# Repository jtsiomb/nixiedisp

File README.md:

nixiedisp - USB nixie tube display
==================================

Nixiedisp is a 6-digit nixie tube numeric display, software-controlled over USB
or RS232, that also functions standalone as a clock.

Features:
  - Controlled over USB or RS232 serial port to display arbitrary numbers, set
    the time/date, change settings, and switch between modes of operation.
  - Standalone operation as a clock or stopwatch timer with a battery-backed
    real-time clock (CR2032 coin cell).
  - Designed to use soviet IN-14 nixie tubes.
  - Powered by a 12v DC supply through a standard 2mm barrel jack (center-positive).

Excercise caution when operating without an enclosure, there are high voltages
(180V DC) present in the power supply section of the board, and around the
nixie tubes.

Project website: http://nuclear.mutantstargoat.com/hw/nixiedisp  
Github repo: https://github.com/jtsiomb/nixiedisp  

Project structure:

 - `hw/`: hardware design
 - `fw/`: firmware for the on-board AVR microcontroller
 - `sw/`: end-user host-side software for controlling the device from a computer

License
-------
Copyright (C) 2020-2021 John Tsiombikas <nuclear@member.fsf.org>

Hardware designs and software (firmware) in this project are free. Feel free to
use, modify, and/or redistribute under the terms of the GNU General Public
License v3, or at your option any later version published by the Free Software
Foundation. See COPYING for details.

How to build a nixiedisp device
-------------------------------
To build one of these for yourself, you need to:

  1. Zip up the contents of the `hw/gerber` directory, and send them to a PCB
     manufacturer to get boards made. For my own boards I used `jlcpcb.com`.

  2. Order the components listed in the bill of materials (`hw/bom.ods`). I
     ordered mine from `mouser.com`, and the spreadsheet contains the mouser
     reference number for each component, to make it easy to order the whole lot
     without too much searching. Make sure to order at least as many of each one
     of them, as specified in the bom.

  3. Find 6 (optionally 4) soviet IN-14 nixie tubes. They tend to go for about
     $10 - $15 each on ebay.

  4. Find a 12v DC power supply with a barrel jack (2mm center pin),
     center-positive (`+ -o)- -`), to power the board. It doesn't have to be
     regulated, but it must be able to provide about 500mA at 12v.
     Typical power consumption is 2-3W.

  5. If you got the git version of this project, you'll need to build the
     firmware by changing into `fw` and typing `make`. You'll need to have
     `avr-gcc`, `libc-avr`, and GNU make installed for this. Release archives
     include a pre-built firmware image you can use (`fw/nixiedisp.hex`).

  6. Assemble the board, and program the microcontroller with a suitable AVR
     ISP. If you have `avrdude` installed, you can simply change into `fw` and
     type `make program`, with the board powered up and the programmer
     connected.

If you don't need the serial port (RS232) option, you can leave J1 (the DB9
connector), U2 (max232 level converter) and all its surrounding electrolytic
capacitors (C1, C2, C4, C8 and C15) unpopulated, and install a 10k pull-up
resistor across the pads of J7 (usbpwr).

References
----------
High-voltage power supply based on Michael Moorrees' nixie supply MK1.5:
https://threeneurons.wordpress.com/nixie-power-supply

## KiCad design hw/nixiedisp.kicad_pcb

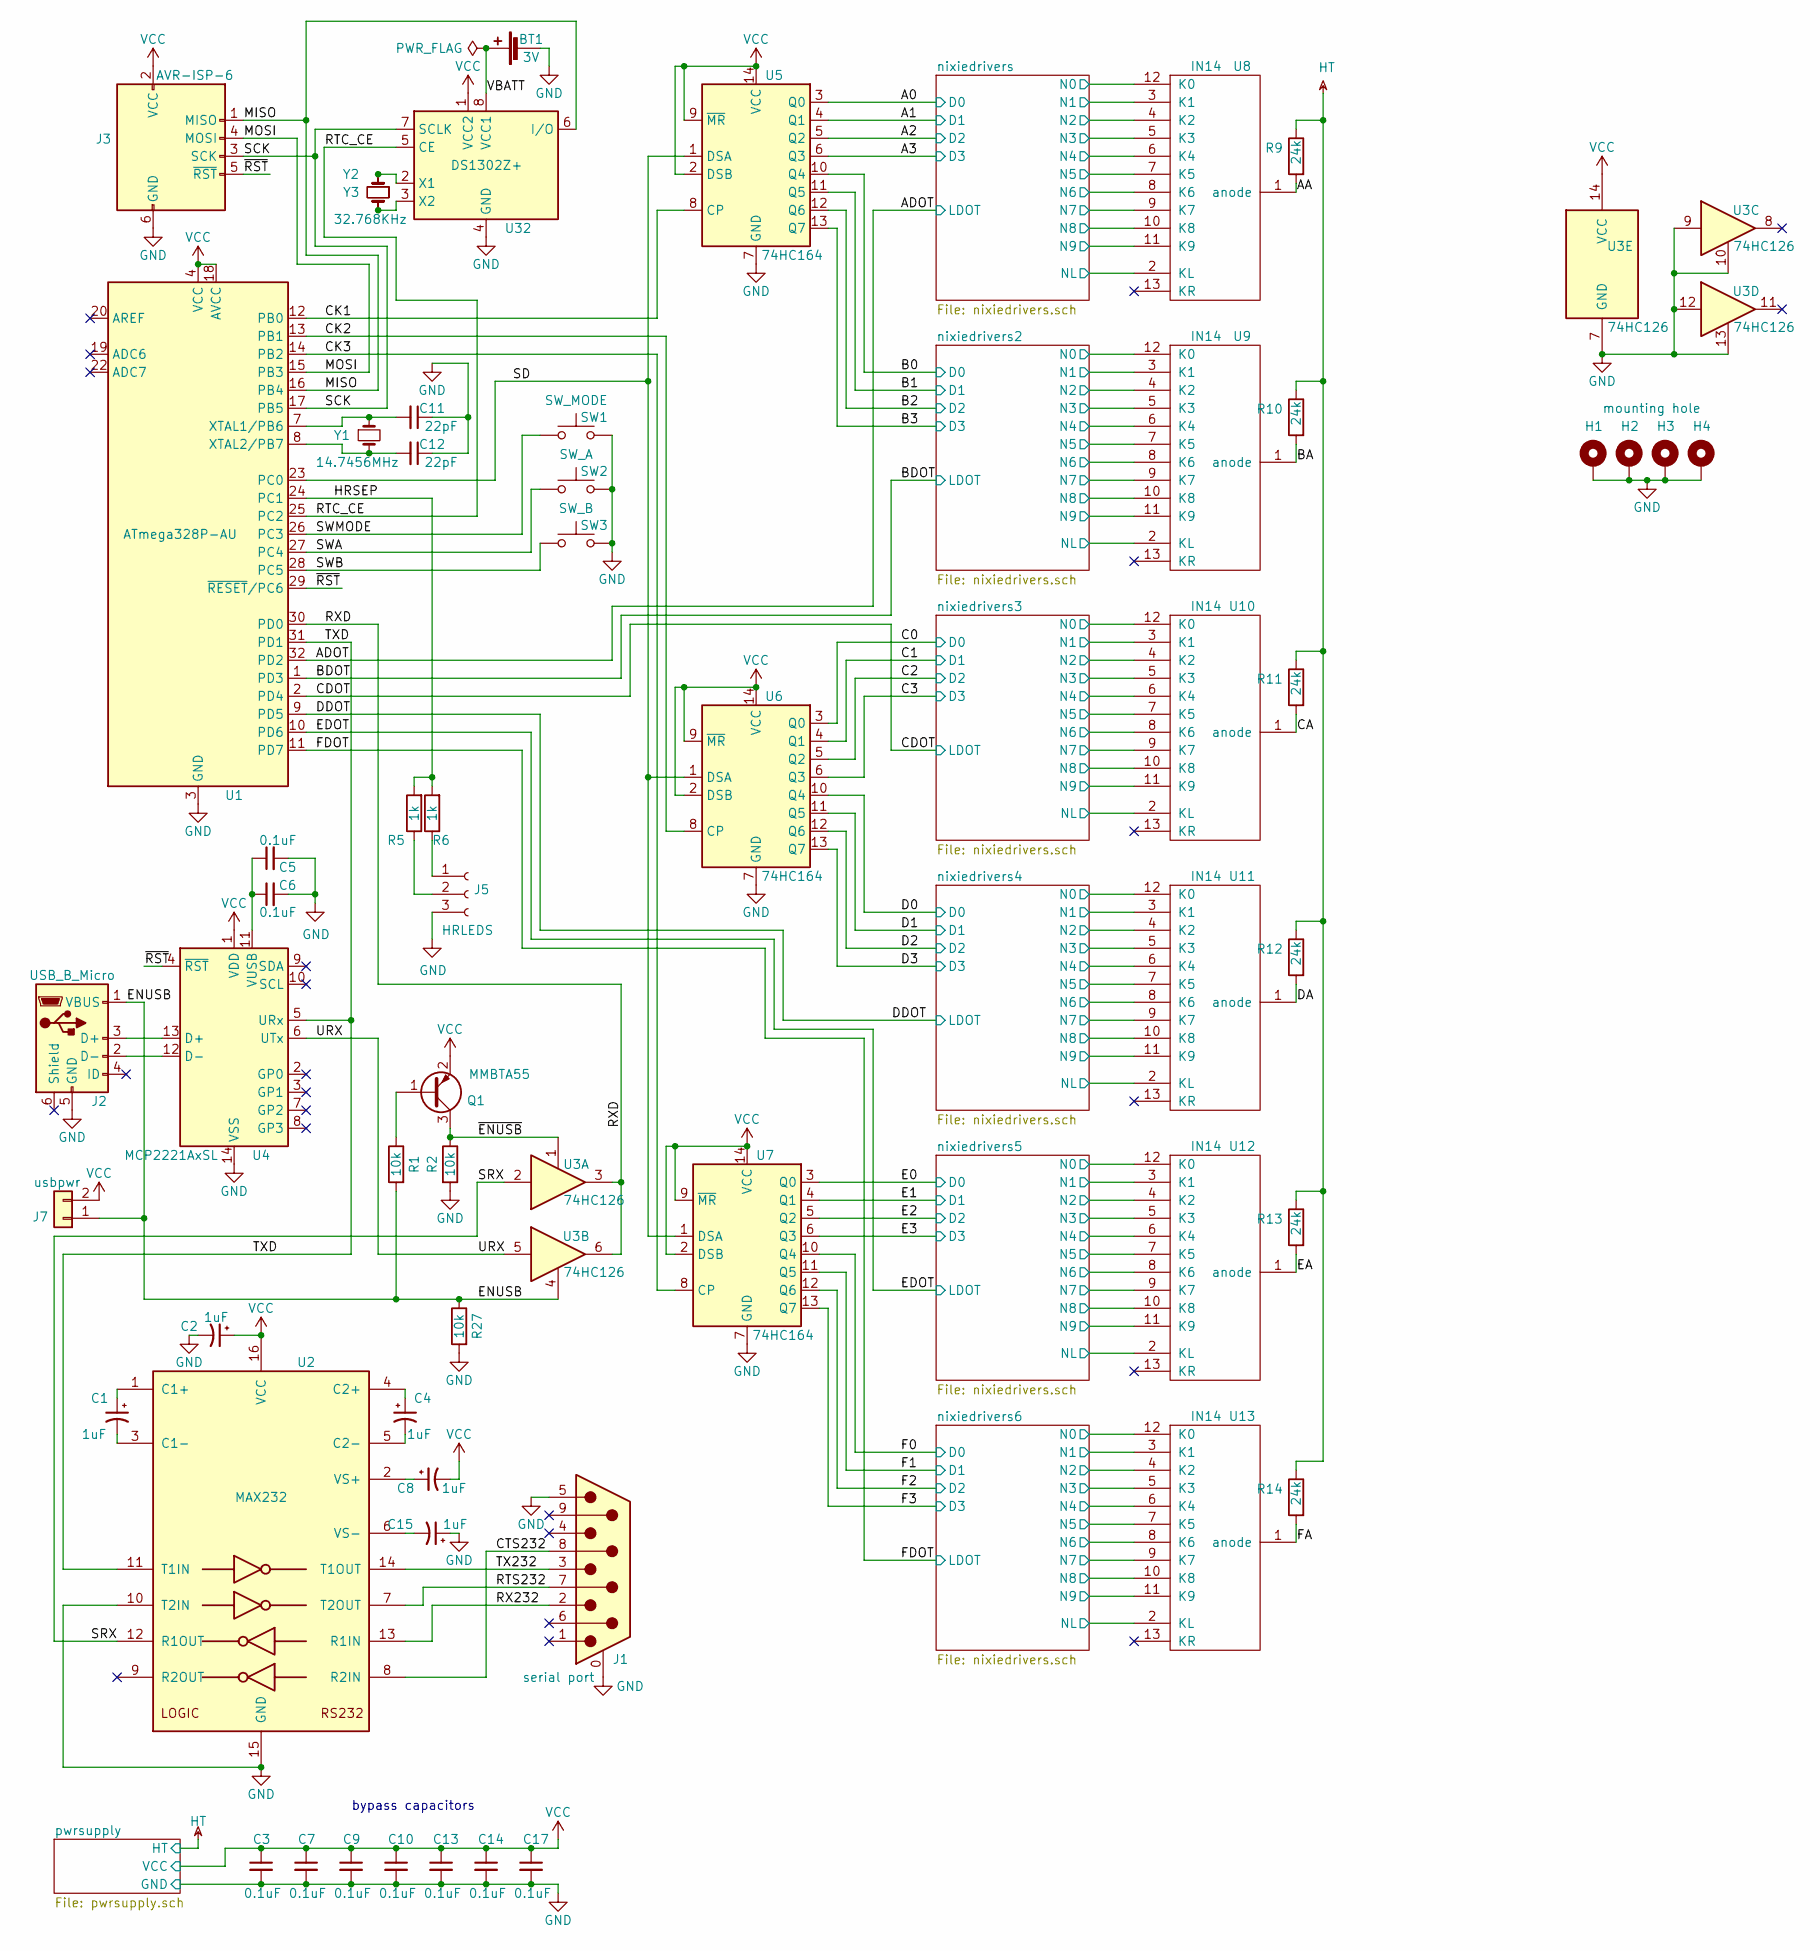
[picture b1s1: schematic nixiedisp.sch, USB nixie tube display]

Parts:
BT1: 3V; BatteryHolder_Keystone_1060_1x2032
C1, C2, C4, C8, C15: 1uF; CP_Elec_4x3.9
C3, C5, C6, C7, C9, C10, C13, C14, C17: 0.1uF; C_0805_2012Metric_Pad1.15x1.40mm_HandSolder
C11, C12: 22pF; C_0805_2012Metric_Pad1.15x1.40mm_HandSolder
H1, H2, H3, H4: mounting hole; MountingHole_3.2mm_M3_Pad_Via
J1: serial port; DSUB-9_Male_Horizontal_P2.77x2.84mm_EdgePinOffset7.70mm_Hou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
J2: USB_B_Micro; USB_Micro-B_Molex-105017-0001
J3: AVR-ISP-6; IDC-Header_2x03_P2.54mm_Vertical
J5: HRLEDS; PinSocket_1x03_P2.54mm_Vertical
J7: usbpwr; PinHeader_1x02_P2.54mm_Vertical
Q1: MMBTA55; SOT-23
R1, R2, R27: 10k; R_0805_2012Metric_Pad1.15x1.40mm_HandSolder
R5, R6: 1k; R_0805_2012Metric_Pad1.15x1.40mm_HandSolder
R9, R10, R11, R12, R13, R14: 24k; R_0805_2012Metric_Pad1.15x1.40mm_HandSolder
SW1: SW_MODE; switch
SW2: SW_A; switch
SW3: SW_B; switch
U1: ATmega328P-AU; TQFP-32_7x7mm_P0.8mm
U2: MAX232; SOIC-16_3.9x9.9mm_P1.27mm
U3: 74HC126; SOIC-14_3.9x8.7mm_P1.27mm
U4: MCP2221AxSL; SOIC-14_3.9x8.7mm_P1.27mm
U5, U6, U7: 74HC164; SOIC-14_3.9x8.7mm_P1.27mm
U8, U9, U10, U11, U12, U13: IN14; nixie_in14
U32: DS1302Z+; SOIC-8_3.9x4.9mm_P1.27mm
Y1: 14.7456MHz; Crystal_SMD_ECS_CSM3X-2Pin_7.6x4.1mm
Y2: 32.768KHz; Crystal_SMD_2012-2Pin_2.0x1.2mm_HandSoldering
Y3: 32.768KHz; Crystal_C38-LF_D3.0mm_L8.0mm_Horizontal

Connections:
/A0: U5.3 (Q0); also elsewhere on the board
/A1: U5.4 (Q1); also elsewhere on the board
/A2: U5.5 (Q2); also elsewhere on the board
/A3: U5.6 (Q3); also elsewhere on the board
/AA: R9.2, U8.1 (anode)
/ADOT: U1.32 (PD2); also elsewhere on the board
/B0: U5.10 (Q4); also elsewhere on the board
/B1: U5.11 (Q5); also elsewhere on the board
/B2: U5.12 (Q6); also elsewhere on the board
/B3: U5.13 (Q7); also elsewhere on the board
/BA: R10.2, U9.1 (anode)
/BDOT: U1.1 (PD3); also elsewhere on the board
/C0: U6.3 (Q0); also elsewhere on the board
/C1: U6.4 (Q1); also elsewhere on the board
/C2: U6.5 (Q2); also elsewhere on the board
/C3: U6.6 (Q3); also elsewhere on the board
/CA: R11.2, U10.1 (anode)
/CDOT: U1.2 (PD4); also elsewhere on the board
/CK1: U1.12 (PB0), U5.8 (CP)
/CK2: U1.13 (PB1), U6.8 (CP)
/CK3: U1.14 (PB2), U7.8 (CP)
/CTS232: J1.8, U2.8 (R2IN)
/D0: U6.10 (Q4); also elsewhere on the board
/D1: U6.11 (Q5); also elsewhere on the board
/D2: U6.12 (Q6); also elsewhere on the board
/D3: U6.13 (Q7); also elsewhere on the board
/DA: R12.2, U11.1 (anode)
/DDOT: U1.9 (PD5); also elsewhere on the board
/E0: U7.3 (Q0); also elsewhere on the board
/E1: U7.4 (Q1); also elsewhere on the board
/E2: U7.5 (Q2); also elsewhere on the board
/E3: U7.6 (Q3); also elsewhere on the board
/EA: R13.2, U12.1 (anode)
/EDOT: U1.10 (PD6); also elsewhere on the board
/ENUSB: J2.1 (VBUS), J7.1, R1.2, R27.1, U3.4
/F0: U7.10 (Q4); also elsewhere on the board
/F1: U7.11 (Q5); also elsewhere on the board
/F2: U7.12 (Q6); also elsewhere on the board
/F3: U7.13 (Q7); also elsewhere on the board
/FA: R14.2, U13.1 (anode)
/FDOT: U1.11 (PD7); also elsewhere on the board
/HRSEP: R5.2, R6.2, U1.24 (PC1)
/MISO: J3.1 (MISO), U1.16 (PB4), U32.6 (I/O)
/MOSI: J3.4 (MOSI), U1.15 (PB3)
/RTC_CE: U1.25 (PC2), U32.5 (CE)
/RTS232: J1.7, U2.7 (T2OUT)
/RX232: J1.2, U2.13 (R1IN)
/RXD: U1.30 (PD0), U3.3, U3.6
/SCK: J3.3 (SCK), U1.17 (PB5), U32.7 (SCLK)
/SD: U1.23 (PC0), U5.1 (DSA), U6.1 (DSA), U7.1 (DSA)
/SRX: U2.12 (R1OUT), U3.2
/SWA: SW2.1, U1.27 (PC4)
/SWB: SW3.1, U1.28 (PC5)
/SWMODE: SW1.1, U1.26 (PC3)
/TX232: J1.3, U2.14 (T1OUT)
/TXD: U1.31 (PD1), U2.11 (T1IN), U4.5 (URx)
/URX: U3.5, U4.6 (UTx)
/VBATT: BT1.1 (+), U32.8 (VCC1)
/nixiedrivers2/N0: U9.12 (K0); also elsewhere on the board
/nixiedrivers2/N1: U9.3 (K1); also elsewhere on the board
/nixiedrivers2/N2: U9.4 (K2); also elsewhere on the board
/nixiedrivers2/N3: U9.5 (K3); also elsewhere on the board
/nixiedrivers2/N4: U9.6 (K4); also elsewhere on the board
/nixiedrivers2/N5: U9.7 (K5); also elsewhere on the board
/nixiedrivers2/N6: U9.8 (K6); also elsewhere on the board
/nixiedrivers2/N7: U9.9 (K7); also elsewhere on the board
/nixiedrivers2/N8: U9.10 (K8); also elsewhere on the board
/nixiedrivers2/N9: U9.11 (K9); also elsewhere on the board
/nixiedrivers2/NL: U9.2 (KL); also elsewhere on the board
/nixiedrivers3/N0: U10.12 (K0); also elsewhere on the board
/nixiedrivers3/N1: U10.3 (K1); also elsewhere on the board
/nixiedrivers3/N2: U10.4 (K2); also elsewhere on the board
/nixiedrivers3/N3: U10.5 (K3); also elsewhere on the board
/nixiedrivers3/N4: U10.6 (K4); also elsewhere on the board
/nixiedrivers3/N5: U10.7 (K5); also elsewhere on the board
/nixiedrivers3/N6: U10.8 (K6); also elsewhere on the board
/nixiedrivers3/N7: U10.9 (K7); also elsewhere on the board
/nixiedrivers3/N8: U10.10 (K8); also elsewhere on the board
/nixiedrivers3/N9: U10.11 (K9); also elsewhere on the board
/nixiedrivers3/NL: U10.2 (KL); also elsewhere on the board
/nixiedrivers4/N0: U11.12 (K0); also elsewhere on the board
/nixiedrivers4/N1: U11.3 (K1); also elsewhere on the board
/nixiedrivers4/N2: U11.4 (K2); also elsewhere on the board
/nixiedrivers4/N3: U11.5 (K3); also elsewhere on the board
/nixiedrivers4/N4: U11.6 (K4); also elsewhere on the board
/nixiedrivers4/N5: U11.7 (K5); also elsewhere on the board
/nixiedrivers4/N6: U11.8 (K6); also elsewhere on the board
/nixiedrivers4/N7: U11.9 (K7); also elsewhere on the board
/nixiedrivers4/N8: U11.10 (K8); also elsewhere on the board
/nixiedrivers4/N9: U11.11 (K9); also elsewhere on the board
/nixiedrivers4/NL: U11.2 (KL); also elsewhere on the board
/nixiedrivers5/N0: U12.12 (K0); also elsewhere on the board
/nixiedrivers5/N1: U12.3 (K1); also elsewhere on the board
/nixiedrivers5/N2: U12.4 (K2); also elsewhere on the board
/nixiedrivers5/N3: U12.5 (K3); also elsewhere on the board
/nixiedrivers5/N4: U12.6 (K4); also elsewhere on the board
/nixiedrivers5/N5: U12.7 (K5); also elsewhere on the board
/nixiedrivers5/N6: U12.8 (K6); also elsewhere on the board
/nixiedrivers5/N7: U12.9 (K7); also elsewhere on the board
/nixiedrivers5/N8: U12.10 (K8); also elsewhere on the board
/nixiedrivers5/N9: U12.11 (K9); also elsewhere on the board
/nixiedrivers5/NL: U12.2 (KL); also elsewhere on the board
/nixiedrivers6/N0: U13.12 (K0); also elsewhere on the board
/nixiedrivers6/N1: U13.3 (K1); also elsewhere on the board
/nixiedrivers6/N2: U13.4 (K2); also elsewhere on the board
/nixiedrivers6/N3: U13.5 (K3); also elsewhere on the board
/nixiedrivers6/N4: U13.6 (K4); also elsewhere on the board
/nixiedrivers6/N5: U13.7 (K5); also elsewhere on the board
/nixiedrivers6/N6: U13.8 (K6); also elsewhere on the board
/nixiedrivers6/N7: U13.9 (K7); also elsewhere on the board
/nixiedrivers6/N8: U13.10 (K8); also elsewhere on the board
/nixiedrivers6/N9: U13.11 (K9); also elsewhere on the board
/nixiedrivers6/NL: U13.2 (KL); also elsewhere on the board
/nixiedrivers/N0: U8.12 (K0); also elsewhere on the board
/nixiedrivers/N1: U8.3 (K1); also elsewhere on the board
/nixiedrivers/N2: U8.4 (K2); also elsewhere on the board
/nixiedrivers/N3: U8.5 (K3); also elsewhere on the board
/nixiedrivers/N4: U8.6 (K4); also elsewhere on the board
/nixiedrivers/N5: U8.7 (K5); also elsewhere on the board
/nixiedrivers/N6: U8.8 (K6); also elsewhere on the board
/nixiedrivers/N7: U8.9 (K7); also elsewhere on the board
/nixiedrivers/N8: U8.10 (K8); also elsewhere on the board
/nixiedrivers/N9: U8.11 (K9); also elsewhere on the board
/nixiedrivers/NL: U8.2 (KL); also elsewhere on the board
/~ENUSB: Q1.3 (C), R2.1, U3.1
/~RST: J3.5 (~RST), U1.29 (~RESET~/PC6), U4.4 (~RST)
GND: BT1.2 (-), C2.2, C3.2, C5.2, C6.2, C7.2, C9.2, C10.2, C11.1, C12.1, C13.2, C14.2, C15.1, C17.2, H1.1, H2.1, H3.1, H4.1, J1.0 (PAD), J1.5, J2.5 (GND), J3.6 (GND), J5.3, R2.2, R27.2, SW1.2, SW2.2, SW3.2, U1.3 (GND), U1.5 (GND), U1.21 (GND), U2.10 (T2IN), U2.15 (GND), U3.7 (GND), U3.9, U3.10, U3.12, U3.13, U4.14 (VSS), U5.7 (GND), U6.7 (GND), U7.7 (GND), U32.4 (GND); also elsewhere on the board
HT: R9.1, R10.1, R11.1, R12.1, R13.1, R14.1; also elsewhere on the board
unnamed: C1.1, U2.1 (C1+)
unnamed: C1.2, U2.3 (C1-)
unnamed: C4.1, U2.4 (C2+)
unnamed: C4.2, U2.5 (C2-)
unnamed: C5.1, C6.1, U4.11 (VUSB)
unnamed: C8.1, U2.2 (VS+)
unnamed: C11.2, U1.7 (XTAL1/PB6), Y1.1
unnamed: C12.2, U1.8 (XTAL2/PB7), Y1.2
unnamed: C15.2, U2.6 (VS-)
unnamed: J2.2 (D-), U4.12 (D-)
unnamed: J2.3 (D+), U4.13 (D+)
unnamed: J5.1, R6.1
unnamed: J5.2, R5.1
unnamed: Q1.1 (B), R1.1
unnamed: U32.2 (X1), Y2.1, Y3.1
unnamed: U32.3 (X2), Y2.2, Y3.2
VCC: C2.1, C3.1, C7.1, C8.2, C9.1, C10.1, C13.1, C14.1, C17.1, J3.2 (VCC), J7.2, Q1.2 (E), U1.4 (VCC), U1.6 (VCC), U1.18 (AVCC), U2.16 (VCC), U3.14 (VCC), U4.1 (VDD), U5.2 (DSB), U5.9 (~MR), U5.14 (VCC), U6.2 (DSB), U6.9 (~MR), U6.14 (VCC), U7.2 (DSB), U7.9 (~MR), U7.14 (VCC), U32.1 (VCC2); also elsewhere on the board

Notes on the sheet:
bypass capacitors

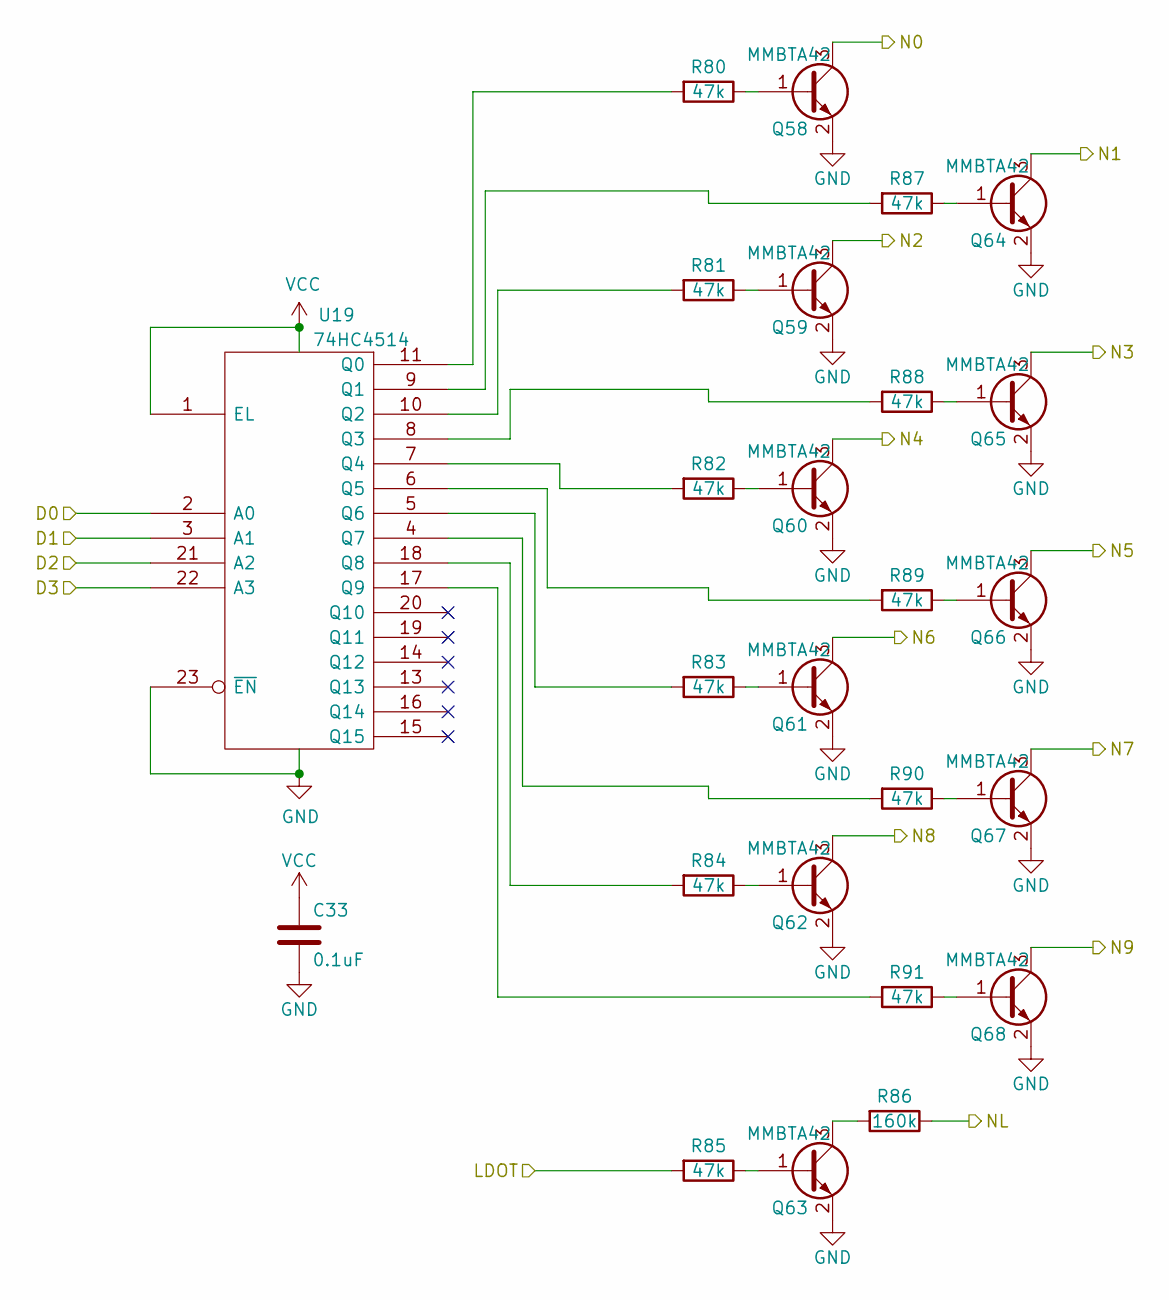
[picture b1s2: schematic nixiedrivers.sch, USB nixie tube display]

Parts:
C18: 0.1uF; C_0805_2012Metric_Pad1.15x1.40mm_HandSolder
Q3, Q4, Q5, Q6, Q7, Q8, Q9, Q10, Q11, Q12, Q13: MMBTA42; SOT-23
R15, R16, R17, R18, R19, R20, R22, R23, R24, R25, R26: 47k; R_0805_2012Metric_Pad1.15x1.40mm_HandSolder
R21: 160k; R_0805_2012Metric_Pad1.15x1.40mm_HandSolder
U14: 74HC4514; SOIC-24W_7.5x15.4mm_P1.27mm

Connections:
/A0: U14.2 (A0); also elsewhere on the board
/A1: U14.3 (A1); also elsewhere on the board
/A2: U14.21 (A2); also elsewhere on the board
/A3: U14.22 (A3); also elsewhere on the board
/ADOT: R20.2; also elsewhere on the board
/nixiedrivers/N0: Q3.3 (C); also elsewhere on the board
/nixiedrivers/N1: Q9.3 (C); also elsewhere on the board
/nixiedrivers/N2: Q4.3 (C); also elsewhere on the board
/nixiedrivers/N3: Q10.3 (C); also elsewhere on the board
/nixiedrivers/N4: Q5.3 (C); also elsewhere on the board
/nixiedrivers/N5: Q11.3 (C); also elsewhere on the board
/nixiedrivers/N6: Q6.3 (C); also elsewhere on the board
/nixiedrivers/N7: Q12.3 (C); also elsewhere on the board
/nixiedrivers/N8: Q7.3 (C); also elsewhere on the board
/nixiedrivers/N9: Q13.3 (C); also elsewhere on the board
/nixiedrivers/NL: R21.1; also elsewhere on the board
GND: C18.2, Q3.2 (E), Q4.2 (E), Q5.2 (E), Q6.2 (E), Q7.2 (E), Q8.2 (E), Q9.2 (E), Q10.2 (E), Q11.2 (E), Q12.2 (E), Q13.2 (E), U14.12 (Vss), U14.23 (~EN); also elsewhere on the board
unnamed: Q3.1 (B), R15.1
unnamed: Q4.1 (B), R16.1
unnamed: Q5.1 (B), R17.1
unnamed: Q6.1 (B), R18.1
unnamed: Q7.1 (B), R19.1
unnamed: Q8.1 (B), R20.1
unnamed: Q8.3 (C), R21.2
unnamed: Q9.1 (B), R22.1
unnamed: Q10.1 (B), R23.1
unnamed: Q11.1 (B), R24.1
unnamed: Q12.1 (B), R25.1
unnamed: Q13.1 (B), R26.1
unnamed: R15.2, U14.11 (Q0)
unnamed: R16.2, U14.10 (Q2)
unnamed: R17.2, U14.7 (Q4)
unnamed: R18.2, U14.5 (Q6)
unnamed: R19.2, U14.18 (Q8)
unnamed: R22.2, U14.9 (Q1)
unnamed: R23.2, U14.8 (Q3)
unnamed: R24.2, U14.6 (Q5)
unnamed: R25.2, U14.4 (Q7)
unnamed: R26.2, U14.17 (Q9)
VCC: C18.1, U14.1 (EL), U14.24 (Vdd); also elsewhere on the board

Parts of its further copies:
C21, C24, C27, C30, C33: 0.1uF; C_0805_2012Metric_Pad1.15x1.40mm_HandSolder
Q14, Q15, Q16, Q17, Q18, Q19, Q20, Q21, Q22, Q23, Q24, Q25, Q26, Q27, Q28, Q29, Q30, Q31, Q32, Q33, Q34, Q35, Q36, Q37, Q38, Q39, Q40, Q41, Q42, Q43, Q44, Q45, Q46, Q47, Q48, Q49, Q50, Q51, Q52, Q53, Q54, Q55, Q56, Q57, Q58, Q59, Q60, Q61, Q62, Q63, Q64, Q65, Q66, Q67, Q68: MMBTA42; SOT-23
R28, R29, R30, R31, R32, R33, R35, R36, R37, R38, R39, R41, R42, R43, R44, R45, R46, R48, R49, R50, R51, R52, R54, R55, R56, R57, R58, R59, R61, R62, R63, R64, R65, R67, R68, R69, R70, R71, R72, R74, R75, R76, R77, R78, R80, R81, R82, R83, R84, R85, R87, R88, R89, R90, R91: 47k; R_0805_2012Metric_Pad1.15x1.40mm_HandSolder
R34, R47, R60, R73, R86: 160k; R_0805_2012Metric_Pad1.15x1.40mm_HandSolder
U15, U16, U17, U18, U19: 74HC4514; SOIC-24W_7.5x15.4mm_P1.27mm

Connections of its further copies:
/B0: U15.2 (A0); also elsewhere on the board
/B1: U15.3 (A1); also elsewhere on the board
/B2: U15.21 (A2); also elsewhere on the board
/B3: U15.22 (A3); also elsewhere on the board
/BDOT: R33.2; also elsewhere on the board
/C0: U16.2 (A0); also elsewhere on the board
/C1: U16.3 (A1); also elsewhere on the board
/C2: U16.21 (A2); also elsewhere on the board
/C3: U16.22 (A3); also elsewhere on the board
/CDOT: R46.2; also elsewhere on the board
/D0: U19.2 (A0); also elsewhere on the board
/D1: U19.3 (A1); also elsewhere on the board
/D2: U19.21 (A2); also elsewhere on the board
/D3: U19.22 (A3); also elsewhere on the board
/DDOT: R85.2; also elsewhere on the board
/E0: U17.2 (A0); also elsewhere on the board
/E1: U17.3 (A1); also elsewhere on the board
/E2: U17.21 (A2); also elsewhere on the board
/E3: U17.22 (A3); also elsewhere on the board
/EDOT: R59.2; also elsewhere on the board
/F0: U18.2 (A0); also elsewhere on the board
/F1: U18.3 (A1); also elsewhere on the board
/F2: U18.21 (A2); also elsewhere on the board
/F3: U18.22 (A3); also elsewhere on the board
/FDOT: R72.2; also elsewhere on the board
/nixiedrivers2/N0: Q14.3 (C); also elsewhere on the board
/nixiedrivers2/N1: Q20.3 (C); also elsewhere on the board
/nixiedrivers2/N2: Q15.3 (C); also elsewhere on the board
/nixiedrivers2/N3: Q21.3 (C); also elsewhere on the board
/nixiedrivers2/N4: Q16.3 (C); also elsewhere on the board
/nixiedrivers2/N5: Q22.3 (C); also elsewhere on the board
/nixiedrivers2/N6: Q17.3 (C); also elsewhere on the board
/nixiedrivers2/N7: Q23.3 (C); also elsewhere on the board
/nixiedrivers2/N8: Q18.3 (C); also elsewhere on the board
/nixiedrivers2/N9: Q24.3 (C); also elsewhere on the board
/nixiedrivers2/NL: R34.1; also elsewhere on the board
/nixiedrivers3/N0: Q25.3 (C); also elsewhere on the board
/nixiedrivers3/N1: Q31.3 (C); also elsewhere on the board
/nixiedrivers3/N2: Q26.3 (C); also elsewhere on the board
/nixiedrivers3/N3: Q32.3 (C); also elsewhere on the board
/nixiedrivers3/N4: Q27.3 (C); also elsewhere on the board
/nixiedrivers3/N5: Q33.3 (C); also elsewhere on the board
/nixiedrivers3/N6: Q28.3 (C); also elsewhere on the board
/nixiedrivers3/N7: Q34.3 (C); also elsewhere on the board
/nixiedrivers3/N8: Q29.3 (C); also elsewhere on the board
/nixiedrivers3/N9: Q35.3 (C); also elsewhere on the board
/nixiedrivers3/NL: R47.1; also elsewhere on the board
/nixiedrivers4/N0: Q58.3 (C); also elsewhere on the board
/nixiedrivers4/N1: Q64.3 (C); also elsewhere on the board
/nixiedrivers4/N2: Q59.3 (C); also elsewhere on the board
/nixiedrivers4/N3: Q65.3 (C); also elsewhere on the board
/nixiedrivers4/N4: Q60.3 (C); also elsewhere on the board
/nixiedrivers4/N5: Q66.3 (C); also elsewhere on the board
/nixiedrivers4/N6: Q61.3 (C); also elsewhere on the board
/nixiedrivers4/N7: Q67.3 (C); also elsewhere on the board
/nixiedrivers4/N8: Q62.3 (C); also elsewhere on the board
/nixiedrivers4/N9: Q68.3 (C); also elsewhere on the board
/nixiedrivers4/NL: R86.1; also elsewhere on the board
/nixiedrivers5/N0: Q36.3 (C); also elsewhere on the board
/nixiedrivers5/N1: Q42.3 (C); also elsewhere on the board
/nixiedrivers5/N2: Q37.3 (C); also elsewhere on the board
/nixiedrivers5/N3: Q43.3 (C); also elsewhere on the board
/nixiedrivers5/N4: Q38.3 (C); also elsewhere on the board
/nixiedrivers5/N5: Q44.3 (C); also elsewhere on the board
/nixiedrivers5/N6: Q39.3 (C); also elsewhere on the board
/nixiedrivers5/N7: Q45.3 (C); also elsewhere on the board
/nixiedrivers5/N8: Q40.3 (C); also elsewhere on the board
/nixiedrivers5/N9: Q46.3 (C); also elsewhere on the board
/nixiedrivers5/NL: R60.1; also elsewhere on the board
/nixiedrivers6/N0: Q47.3 (C); also elsewhere on the board
/nixiedrivers6/N1: Q53.3 (C); also elsewhere on the board
/nixiedrivers6/N2: Q48.3 (C); also elsewhere on the board
/nixiedrivers6/N3: Q54.3 (C); also elsewhere on the board
/nixiedrivers6/N4: Q49.3 (C); also elsewhere on the board
/nixiedrivers6/N5: Q55.3 (C); also elsewhere on the board
/nixiedrivers6/N6: Q50.3 (C); also elsewhere on the board
/nixiedrivers6/N7: Q56.3 (C); also elsewhere on the board
/nixiedrivers6/N8: Q51.3 (C); also elsewhere on the board
/nixiedrivers6/N9: Q57.3 (C); also elsewhere on the board
/nixiedrivers6/NL: R73.1; also elsewhere on the board
GND: C21.2, C24.2, C27.2, C30.2, C33.2, Q14.2 (E), Q15.2 (E), Q16.2 (E), Q17.2 (E), Q18.2 (E), Q19.2 (E), Q20.2 (E), Q21.2 (E), Q22.2 (E), Q23.2 (E), Q24.2 (E), Q25.2 (E), Q26.2 (E), Q27.2 (E), Q28.2 (E), Q29.2 (E), Q30.2 (E), Q31.2 (E), Q32.2 (E), Q33.2 (E), Q34.2 (E), Q35.2 (E), Q36.2 (E), Q37.2 (E), Q38.2 (E), Q39.2 (E), Q40.2 (E), Q41.2 (E), Q42.2 (E), Q43.2 (E), Q44.2 (E), Q45.2 (E), Q46.2 (E), Q47.2 (E), Q48.2 (E), Q49.2 (E), Q50.2 (E), Q51.2 (E), Q52.2 (E), Q53.2 (E), Q54.2 (E), Q55.2 (E), Q56.2 (E), Q57.2 (E), Q58.2 (E), Q59.2 (E), Q60.2 (E), Q61.2 (E), Q62.2 (E), Q63.2 (E), Q64.2 (E), Q65.2 (E), Q66.2 (E), Q67.2 (E), Q68.2 (E), U15.12 (Vss), U15.23 (~EN), U16.12 (Vss), U16.23 (~EN), U17.12 (Vss), U17.23 (~EN), U18.12 (Vss), U18.23 (~EN), U19.12 (Vss), U19.23 (~EN); also elsewhere on the board
unnamed: Q14.1 (B), R28.1
unnamed: Q15.1 (B), R29.1
unnamed: Q16.1 (B), R30.1
unnamed: Q17.1 (B), R31.1
unnamed: Q18.1 (B), R32.1
unnamed: Q19.1 (B), R33.1
unnamed: Q19.3 (C), R34.2
unnamed: Q20.1 (B), R35.1
unnamed: Q21.1 (B), R36.1
unnamed: Q22.1 (B), R37.1
unnamed: Q23.1 (B), R38.1
unnamed: Q24.1 (B), R39.1
unnamed: Q25.1 (B), R41.1
unnamed: Q26.1 (B), R42.1
unnamed: Q27.1 (B), R43.1
unnamed: Q28.1 (B), R44.1
unnamed: Q29.1 (B), R45.1
unnamed: Q30.1 (B), R46.1
unnamed: Q30.3 (C), R47.2
unnamed: Q31.1 (B), R48.1
unnamed: Q32.1 (B), R49.1
unnamed: Q33.1 (B), R50.1
unnamed: Q34.1 (B), R51.1
unnamed: Q35.1 (B), R52.1
unnamed: Q36.1 (B), R54.1
unnamed: Q37.1 (B), R55.1
unnamed: Q38.1 (B), R56.1
unnamed: Q39.1 (B), R57.1
unnamed: Q40.1 (B), R58.1
unnamed: Q41.1 (B), R59.1
unnamed: Q41.3 (C), R60.2
unnamed: Q42.1 (B), R61.1
unnamed: Q43.1 (B), R62.1
unnamed: Q44.1 (B), R63.1
unnamed: Q45.1 (B), R64.1
unnamed: Q46.1 (B), R65.1
unnamed: Q47.1 (B), R67.1
unnamed: Q48.1 (B), R68.1
unnamed: Q49.1 (B), R69.1
unnamed: Q50.1 (B), R70.1
unnamed: Q51.1 (B), R71.1
unnamed: Q52.1 (B), R72.1
unnamed: Q52.3 (C), R73.2
unnamed: Q53.1 (B), R74.1
unnamed: Q54.1 (B), R75.1
unnamed: Q55.1 (B), R76.1
unnamed: Q56.1 (B), R77.1
unnamed: Q57.1 (B), R78.1
unnamed: Q58.1 (B), R80.1
unnamed: Q59.1 (B), R81.1
unnamed: Q60.1 (B), R82.1
unnamed: Q61.1 (B), R83.1
unnamed: Q62.1 (B), R84.1
unnamed: Q63.1 (B), R85.1
unnamed: Q63.3 (C), R86.2
unnamed: Q64.1 (B), R87.1
unnamed: Q65.1 (B), R88.1
unnamed: Q66.1 (B), R89.1
unnamed: Q67.1 (B), R90.1
unnamed: Q68.1 (B), R91.1
unnamed: R28.2, U15.11 (Q0)
unnamed: R29.2, U15.10 (Q2)
unnamed: R30.2, U15.7 (Q4)
unnamed: R31.2, U15.5 (Q6)
unnamed: R32.2, U15.18 (Q8)
unnamed: R35.2, U15.9 (Q1)
unnamed: R36.2, U15.8 (Q3)
unnamed: R37.2, U15.6 (Q5)
unnamed: R38.2, U15.4 (Q7)
unnamed: R39.2, U15.17 (Q9)
unnamed: R41.2, U16.11 (Q0)
unnamed: R42.2, U16.10 (Q2)
unnamed: R43.2, U16.7 (Q4)
unnamed: R44.2, U16.5 (Q6)
unnamed: R45.2, U16.18 (Q8)
unnamed: R48.2, U16.9 (Q1)
unnamed: R49.2, U16.8 (Q3)
unnamed: R50.2, U16.6 (Q5)
unnamed: R51.2, U16.4 (Q7)
unnamed: R52.2, U16.17 (Q9)
unnamed: R54.2, U17.11 (Q0)
unnamed: R55.2, U17.10 (Q2)
unnamed: R56.2, U17.7 (Q4)
unnamed: R57.2, U17.5 (Q6)
unnamed: R58.2, U17.18 (Q8)
unnamed: R61.2, U17.9 (Q1)
unnamed: R62.2, U17.8 (Q3)
unnamed: R63.2, U17.6 (Q5)
unnamed: R64.2, U17.4 (Q7)
unnamed: R65.2, U17.17 (Q9)
unnamed: R67.2, U18.11 (Q0)
unnamed: R68.2, U18.10 (Q2)
unnamed: R69.2, U18.7 (Q4)
unnamed: R70.2, U18.5 (Q6)
unnamed: R71.2, U18.18 (Q8)
unnamed: R74.2, U18.9 (Q1)
unnamed: R75.2, U18.8 (Q3)
unnamed: R76.2, U18.6 (Q5)
unnamed: R77.2, U18.4 (Q7)
unnamed: R78.2, U18.17 (Q9)
unnamed: R80.2, U19.11 (Q0)
unnamed: R81.2, U19.10 (Q2)
unnamed: R82.2, U19.7 (Q4)
unnamed: R83.2, U19.5 (Q6)
unnamed: R84.2, U19.18 (Q8)
unnamed: R87.2, U19.9 (Q1)
unnamed: R88.2, U19.8 (Q3)
unnamed: R89.2, U19.6 (Q5)
unnamed: R90.2, U19.4 (Q7)
unnamed: R91.2, U19.17 (Q9)
VCC: C21.1, C24.1, C27.1, C30.1, C33.1, U15.1 (EL), U15.24 (Vdd), U16.1 (EL), U16.24 (Vdd), U17.1 (EL), U17.24 (Vdd), U18.1 (EL), U18.24 (Vdd), U19.1 (EL), U19.24 (Vdd); also elsewhere on the board

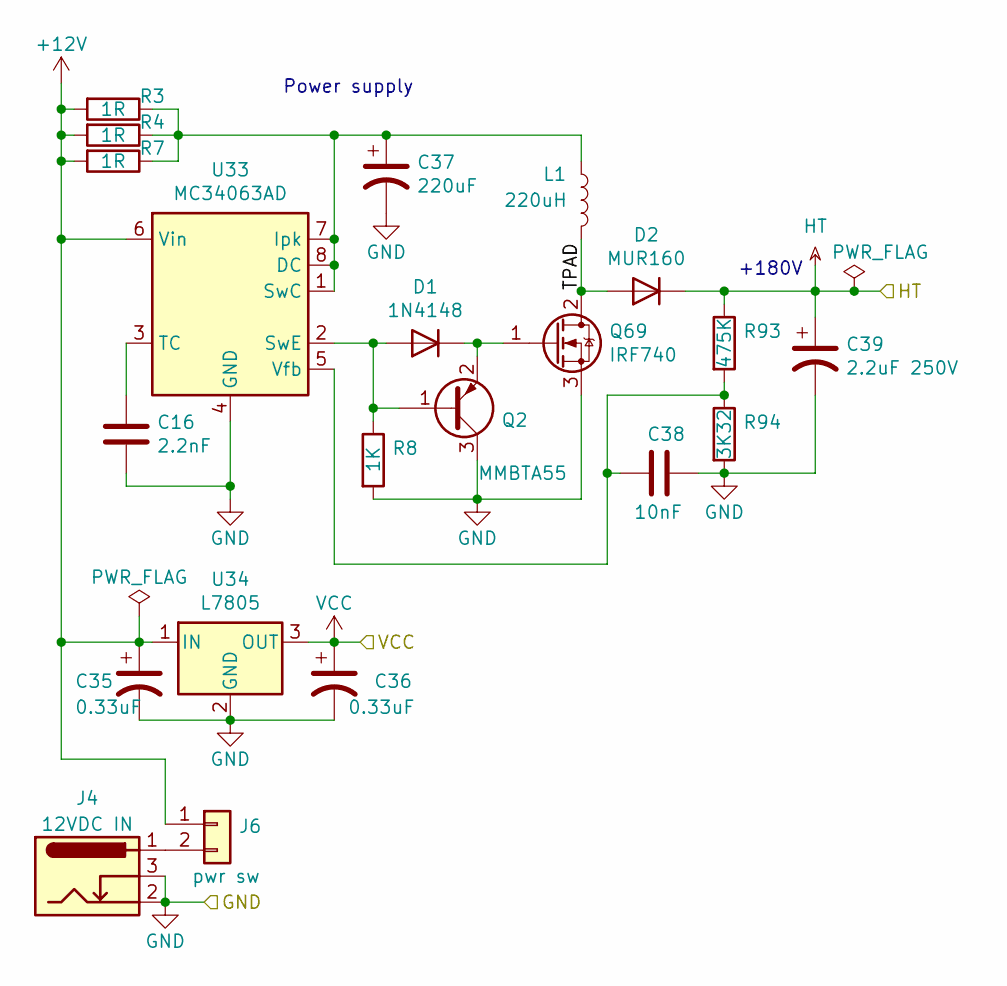
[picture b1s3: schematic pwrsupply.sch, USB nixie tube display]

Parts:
C16: 2.2nF; C_0805_2012Metric_Pad1.15x1.40mm_HandSolder
C35, C36: 0.33uF; CP_Elec_4x5.4
C37: 220uF; CP_Elec_8x10
C38: 10nF; C_0805_2012Metric_Pad1.15x1.40mm_HandSolder
C39: 2.2uF 250V; CP_Radial_D6.3mm_P2.50mm_Horizontal
D1: 1N4148; D_0805_2012Metric_Pad1.15x1.40mm_HandSolder
D2: MUR160; D_SMA-SMB_Universal_Handsoldering
J4: 12VDC IN; BarrelJack_Horizontal
J6: pwr sw; PinHeader_1x02_P2.54mm_Vertical
L1: 220uH; L_Bourns_SDR1806
Q2: MMBTA55; SOT-23
Q69: IRF740; TO-263-2
R3, R4, R7: 1R; R_0805_2012Metric_Pad1.15x1.40mm_HandSolder
R8: 1K; R_0805_2012Metric_Pad1.15x1.40mm_HandSolder
R93: 475K; R_0805_2012Metric_Pad1.15x1.40mm_HandSolder
R94: 3K32; R_0805_2012Metric_Pad1.15x1.40mm_HandSolder
U33: MC34063AD; SOIC-8_3.9x4.9mm_P1.27mm
U34: L7805; TO-252-2

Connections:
+12V: C35.1, J6.1, R3.2, R4.2, R7.2, U33.6 (Vin), U34.1 (IN)
/pwrsupply/TPAD: D2.2 (A), L1.2, Q69.2 (D)
GND: C16.2, C35.2, C36.2, C37.2, C38.1, C39.2, J4.2, J4.3, Q2.3 (C), Q69.3 (S), R8.2, R94.2, U33.4 (GND), U34.2 (GND); also elsewhere on the board
HT: C39.1, D2.1 (K), R93.1; also elsewhere on the board
unnamed: C16.1, U33.3 (TC)
unnamed: C37.1, L1.1, R3.1, R4.1, R7.1, U33.1 (SwC), U33.7 (Ipk), U33.8 (DC)
unnamed: C38.2, R93.2, R94.1, U33.5 (Vfb)
unnamed: D1.1 (K), Q2.2 (E), Q69.1 (G)
unnamed: D1.2 (A), Q2.1 (B), R8.1, U33.2 (SwE)
unnamed: J4.1, J6.2
VCC: C36.1, U34.3 (OUT); also elsewhere on the board

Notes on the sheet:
+180V
Power supply

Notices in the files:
hw/nixiedisp.kicad_pcb:
License: GNU General Public License v3 (or later)
Copyright © 2020-2021 John Tsiombikas
Free hw design GNU GPLv3 or later
hw/nixiedisp.sch:
Free hardware design. License: GNU GPLv3 (or later)
Copyright © John Tsiombikas
